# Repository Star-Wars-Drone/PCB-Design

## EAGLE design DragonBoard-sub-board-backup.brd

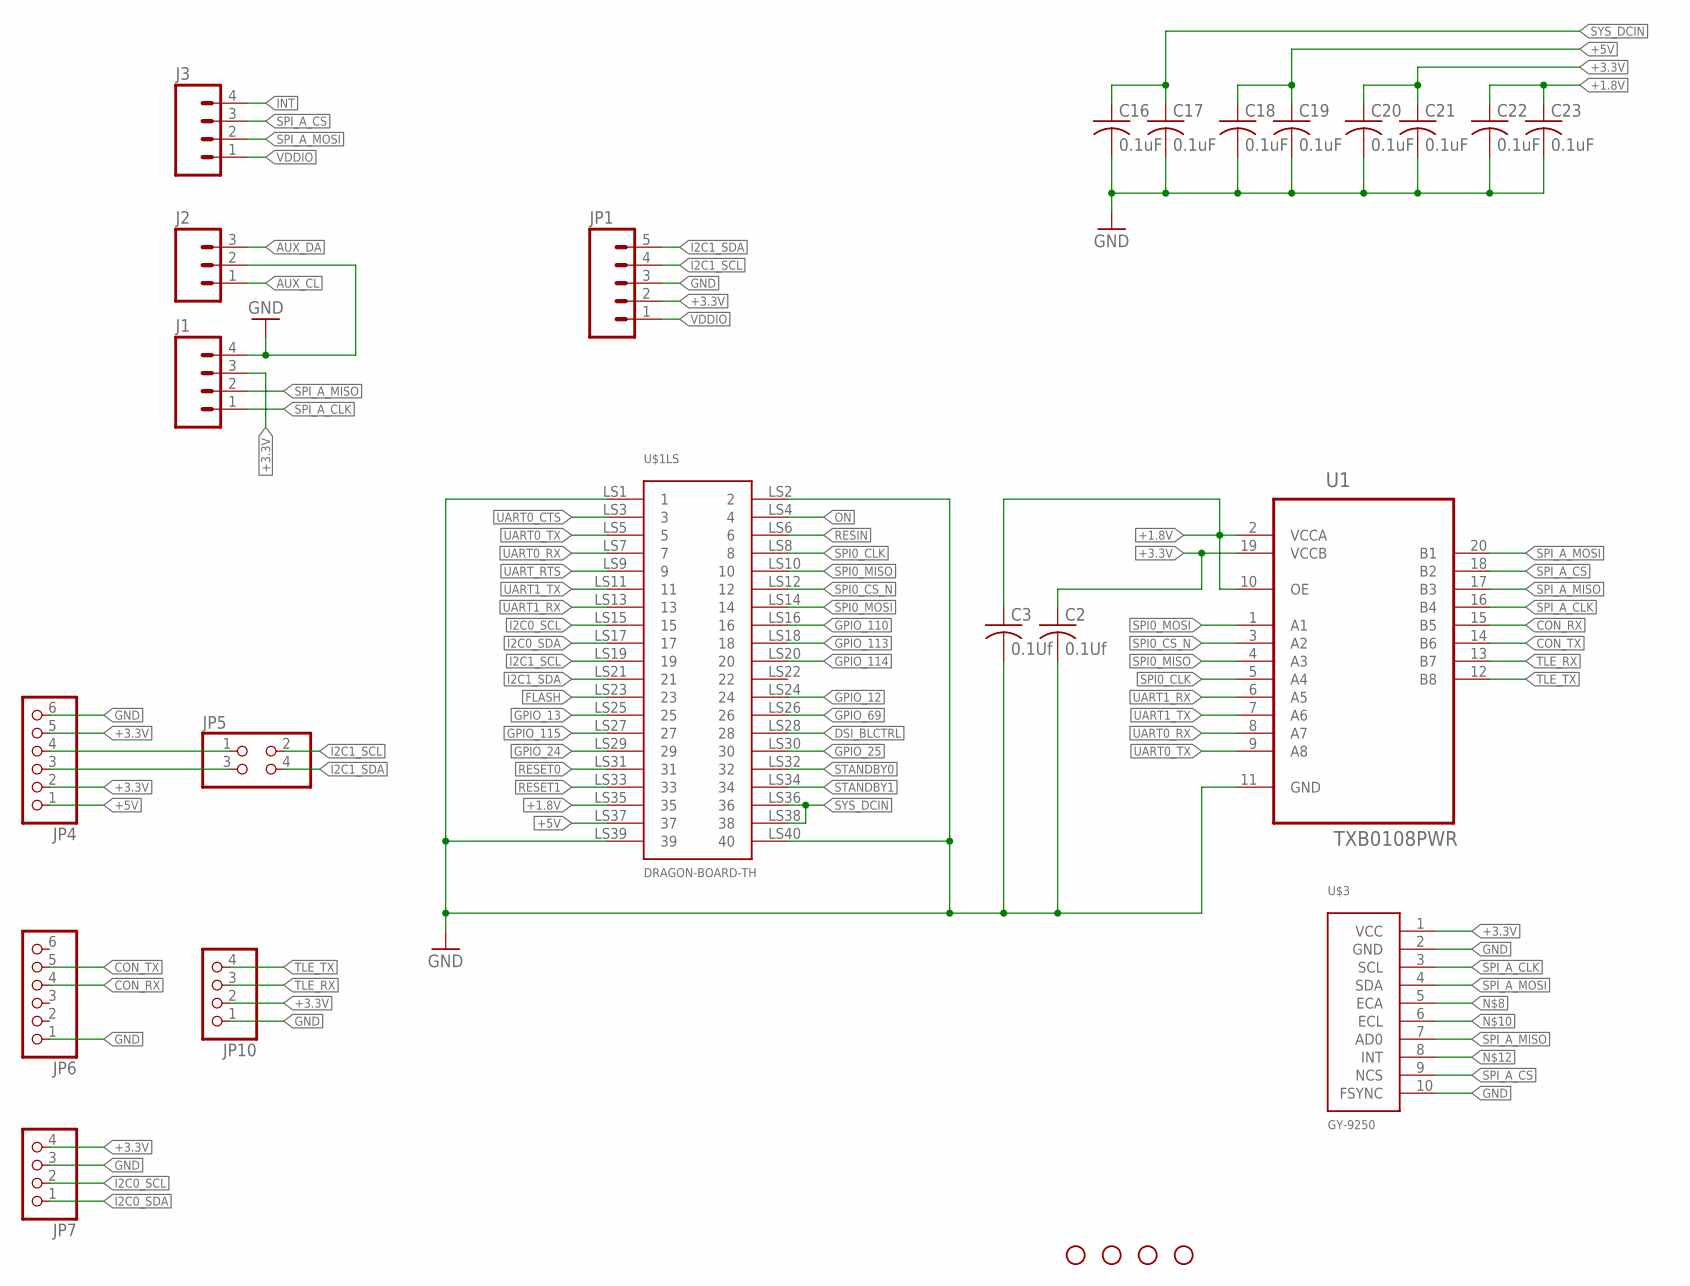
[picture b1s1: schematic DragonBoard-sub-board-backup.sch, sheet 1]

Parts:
C2, C3: 0.1Uf; C0402
C16, C17, C18, C19, C20, C21, C22, C23: 0.1uF; C0402
J1, J3: M04PTH; 1X04
J2: M03PTH; 1X03
JP1: M05_ROUNDONLY_NOSILK; 1X05_ROUNDONLY_NOSILK
JP4, JP6: PINHD-1X6; 1X06
JP5: PINHD-2X2; 2X02
JP7, JP10: PINHD-1X4; 1X04
STANDOFF1, STANDOFF2, STANDOFF3, STANDOFF4: STAND-OFF
U1: TXB0108PWR; SOP65P640X120-20N
U$1: DRAGON-BOARD-TH; DROGENBOARD-TH
U$3: GY-9250; IMU

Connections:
+1.8V: C3.1, C22.1, C23.1, U1.2 (VCCA), U1.10 (OE), U$1.LS35 (35); also elsewhere on the board
+3.3V: C2.1, C20.1, C21.1, J1.3, JP1.2, JP4.2, JP4.5, JP7.4, JP10.2, U1.19 (VCCB), U$3.1 (VCC); also elsewhere on the board
+5V: C18.1, C19.1, JP4.1, U$1.LS37 (37); also elsewhere on the board
AUX_CL: J2.1
AUX_DA: J2.3
CON_RX: JP6.4, U1.15 (B5)
CON_TX: JP6.5, U1.14 (B6)
DSI_BLCTRL: U$1.LS28 (28)
FLASH: U$1.LS23 (23); also elsewhere on the board
GND: C2.2, C3.2, C16.2, C17.2, C18.2, C19.2, C20.2, C21.2, C22.2, C23.2, J1.4, J2.2, JP1.3, JP4.6, JP6.1, JP7.3, JP10.1, U1.11 (GND), U$1.LS1 (1), U$1.LS2 (2), U$1.LS39 (39), U$1.LS40 (40), U$3.2 (GND), U$3.10 (FSYNC); also elsewhere on the board
GPIO_12: U$1.LS24 (24)
GPIO_13: U$1.LS25 (25)
GPIO_24: U$1.LS29 (29)
GPIO_25: U$1.LS30 (30)
GPIO_69: U$1.LS26 (26)
GPIO_110: U$1.LS16 (16)
GPIO_113: U$1.LS18 (18)
GPIO_114: U$1.LS20 (20)
GPIO_115: U$1.LS27 (27)
I2C0_SCL: JP7.2, U$1.LS15 (15)
I2C0_SDA: JP7.1, U$1.LS17 (17)
I2C1_SCL: JP1.4, JP5.2, U$1.LS19 (19); also elsewhere on the board
I2C1_SDA: JP1.5, JP5.4, U$1.LS21 (21); also elsewhere on the board
INT: J3.4
unnamed: JP4.4, JP5.1
unnamed: JP4.3, JP5.3
ON: U$1.LS4 (4)
RESET0: U$1.LS31 (31); also elsewhere on the board
RESET1: U$1.LS33 (33); also elsewhere on the board
RESIN: U$1.LS6 (6)
SPI0_CLK: U1.5 (A4), U$1.LS8 (8)
SPI0_CS_N: U1.3 (A2), U$1.LS12 (12)
SPI0_MISO: U1.4 (A3), U$1.LS10 (10)
SPI0_MOSI: U1.1 (A1), U$1.LS14 (14)
SPI_A_CLK: J1.1, U1.16 (B4), U$3.3 (SCL)
SPI_A_CS: J3.3, U1.18 (B2), U$3.9 (NCS)
SPI_A_MISO: J1.2, U1.17 (B3), U$3.7 (AD0)
SPI_A_MOSI: J3.2, U1.20 (B1), U$3.4 (SDA)
STANDBY0: U$1.LS32 (32); also elsewhere on the board
STANDBY1: U$1.LS34 (34); also elsewhere on the board
SYS_DCIN: C16.1, C17.1, U$1.LS36 (36), U$1.LS38 (38); also elsewhere on the board
TLE_RX: JP10.3, U1.13 (B7)
TLE_TX: JP10.4, U1.12 (B8)
UART0_CTS: U$1.LS3 (3)
UART0_RX: U1.8 (A7), U$1.LS7 (7)
UART0_TX: U1.9 (A8), U$1.LS5 (5)
UART1_RX: U1.6 (A5), U$1.LS13 (13)
UART1_TX: U1.7 (A6), U$1.LS11 (11)
UART_RTS: U$1.LS9 (9)
VDDIO: J3.1, JP1.1

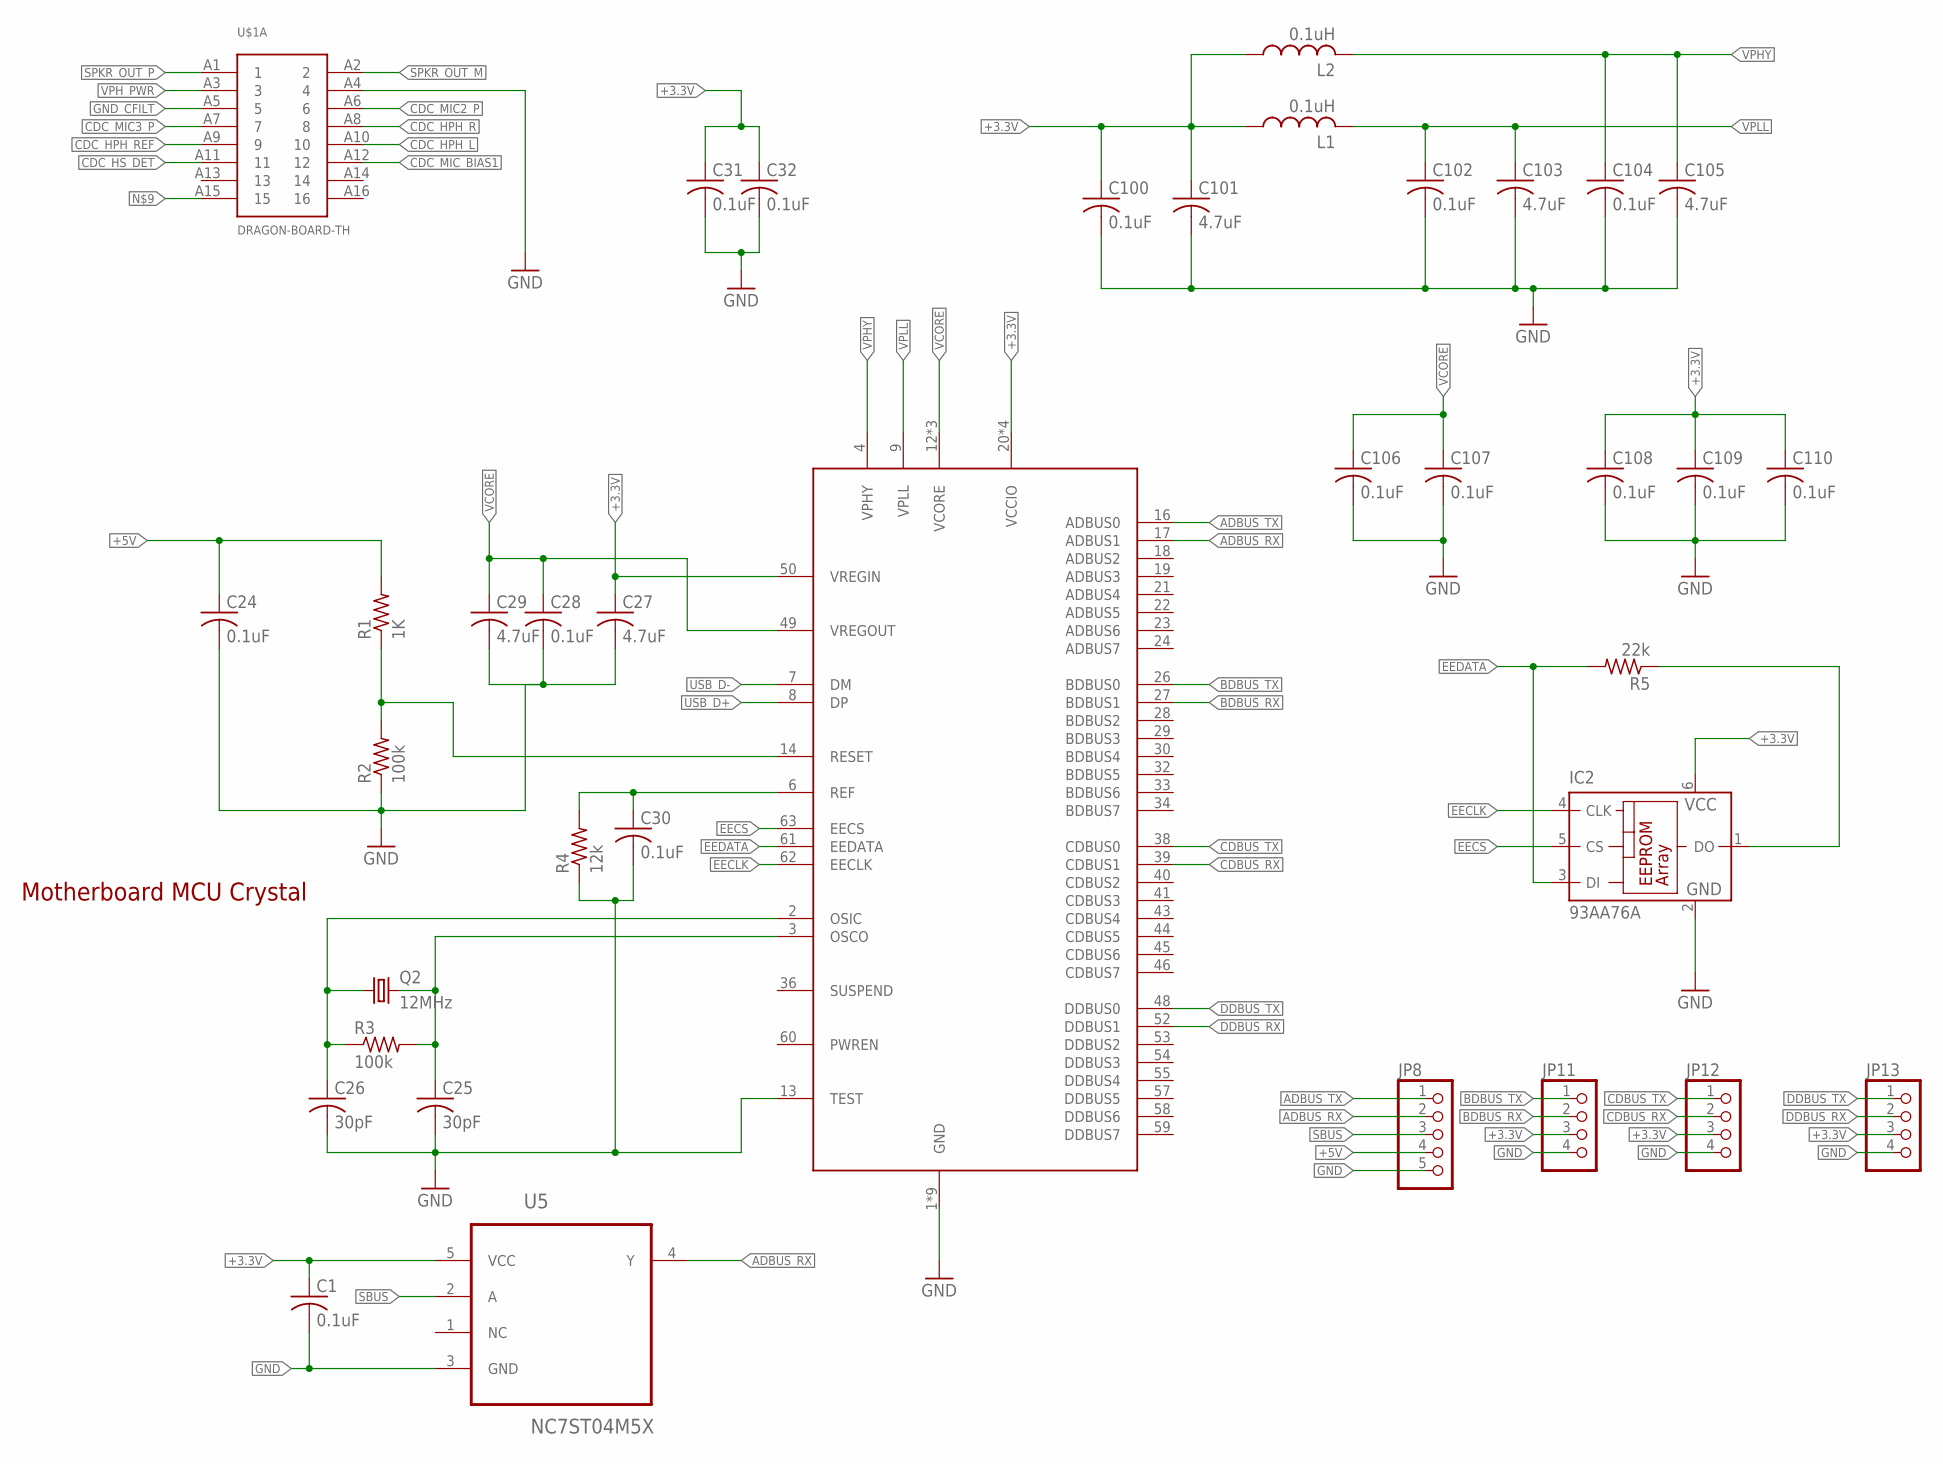
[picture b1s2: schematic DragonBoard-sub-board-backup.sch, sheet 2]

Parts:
C1, C24, C28, C30, C100, C102, C104, C106, C107, C108, C109, C110: 0.1uF; C0402
C25, C26: 30pF; C0402
C27, C29, C101, C103, C105: 4.7uF; C0402
C31, C32: 0.1uF; C0805
IC2: 93AA76A; SOT23-6
JP8: PINHD-1X5; 1X05
JP11, JP12, JP13: PINHD-1X4; 1X04
L1, L2: 0.1uH; L3216C
Q2: 12MHz; CTS406
R1: 1K; R0402
R2, R3: 100k; R0402
R4: 12k; R0402
R5: 22k; R0402
U5: NC7ST04M5X; SOT95P280X145-5N
U$1: DRAGON-BOARD-TH; DROGENBOARD-TH
U$4: FT423H; LQFP-64

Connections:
+3.3V: C1.1, C27.1, C31.1, C32.1, C100.1, C101.1, C108.1, C109.1, C110.1, IC2.6 (VCC), JP11.3, JP12.3, JP13.3, L1.1, L2.1, U5.5 (VCC), U$4.20 (VCCIO), U$4.31 (VCCIO), U$4.42 (VCCIO), U$4.50 (VREGIN), U$4.56 (VCCIO); also elsewhere on the board
+5V: C24.1, JP8.4, R1.2; also elsewhere on the board
ADBUS_RX: JP8.2, U5.4 (Y), U$4.17 (ADBUS1)
ADBUS_TX: JP8.1, U$4.16 (ADBUS0)
BDBUS_RX: JP11.2, U$4.27 (BDBUS1)
BDBUS_TX: JP11.1, U$4.26 (BDBUS0)
CDBUS_RX: JP12.2, U$4.39 (CDBUS1)
CDBUS_TX: JP12.1, U$4.38 (CDBUS0)
CDC_HPH_L: U$1.A10 (10)
CDC_HPH_R: U$1.A8 (8)
CDC_HPH_REF: U$1.A9 (9)
CDC_HS_DET: U$1.A11 (11)
CDC_MIC2_P: U$1.A6 (6)
CDC_MIC3_P: U$1.A7 (7)
CDC_MIC_BIAS1: U$1.A12 (12)
DDBUS_RX: JP13.2, U$4.52 (DDBUS1)
DDBUS_TX: JP13.1, U$4.48 (DDBUS0)
EECLK: IC2.4 (CLK), U$4.62 (EECLK)
EECS: IC2.5 (CS), U$4.63 (EECS)
EEDATA: IC2.3 (DI), R5.2, U$4.61 (EEDATA)
GND: C1.2, C24.2, C25.2, C26.2, C27.2, C28.2, C29.2, C30.2, C31.2, C32.2, C100.2, C101.2, C102.2, C103.2, C104.2, C105.2, C106.2, C107.2, C108.2, C109.2, C110.2, IC2.2 (GND), JP8.5, JP11.4, JP12.4, JP13.4, R2.1, R4.1, U5.3 (GND), U$1.A4 (4), U$4.1 (GND), U$4.5 (GND), U$4.10 (GND), U$4.11 (GND), U$4.13 (TEST), U$4.15 (GND), U$4.25 (GND), U$4.35 (GND), U$4.47 (GND), U$4.51 (GND); also elsewhere on the board
GND_CFILT: U$1.A5 (5)
unnamed: C30.1, R4.2, U$4.6 (REF)
unnamed: C26.1, Q2.1, R3.1, U$4.2 (OSIC)
unnamed: C25.1, Q2.3 (2), R3.2, U$4.3 (OSCO)
unnamed: IC2.1 (DO), R5.1
unnamed: R1.1, R2.2, U$4.14 (RESET)
SBUS: JP8.3, U5.2 (A)
SPKR_OUT_M: U$1.A2 (2)
SPKR_OUT_P: U$1.A1 (1)
USB_D+: U$4.8 (DP); also elsewhere on the board
USB_D-: U$4.7 (DM); also elsewhere on the board
VCORE: C28.1, C29.1, C106.1, C107.1, U$4.12 (VCORE), U$4.37 (VCORE), U$4.49 (VREGOUT), U$4.64 (VCORE)
VPHY: C104.1, C105.1, L2.2, U$4.4 (VPHY)
VPH_PWR: U$1.A3 (3)
VPLL: C102.1, C103.1, L1.2, U$4.9 (VPLL)

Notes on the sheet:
Motherboard MCU Crystal

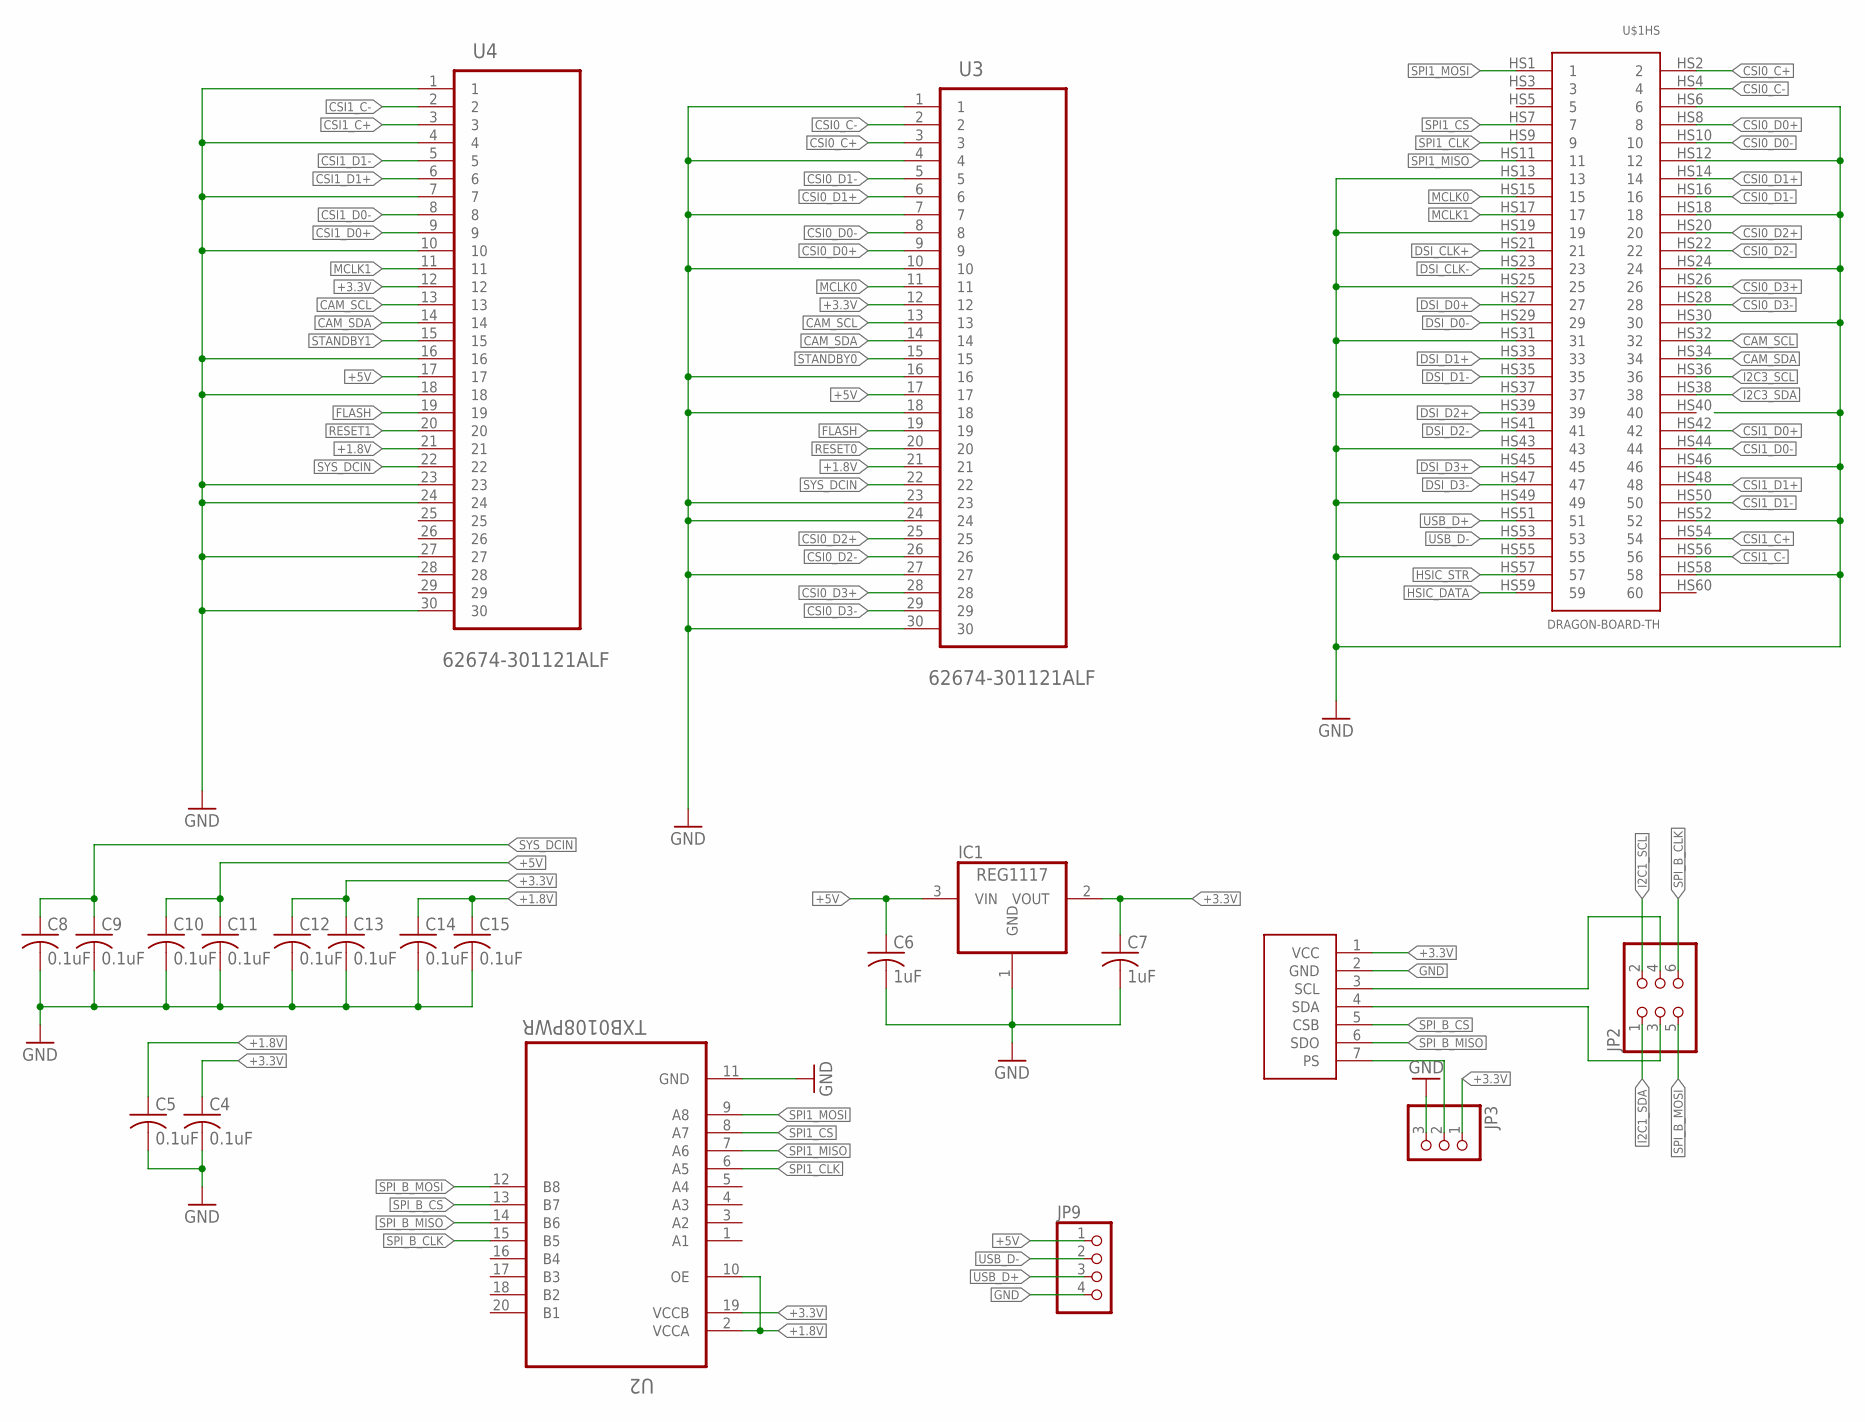
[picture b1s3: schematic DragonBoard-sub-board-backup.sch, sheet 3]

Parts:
C4, C5, C8, C9, C10, C11, C12, C13, C14, C15: 0.1uF; C0402
C6, C7: 1uF; C0402
IC1: REG1117; SOT223
JP2: PINHD-2X3; 2X03
JP3: PINHD-1X3; 1X03
JP9: PINHD-1X4; 1X04
U2: TXB0108PWR; SOP65P640X120-20N
U3, U4: 62674-301121ALF; FCI_62674-301121ALF
U$1: DRAGON-BOARD-TH; DROGENBOARD-TH
U$2: GY-63; BURO

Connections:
+1.8V: C5.1, C14.1, C15.1, U2.2 (VCCA), U2.10 (OE), U3.21, U4.21; also elsewhere on the board
+3.3V: C4.1, C7.1, C12.1, C13.1, IC1.2 (VOUT), JP3.1, U2.19 (VCCB), U3.12, U4.12, U$2.1 (VCC); also elsewhere on the board
+5V: C6.1, C10.1, C11.1, IC1.3 (VIN), JP9.1, U3.17, U4.17; also elsewhere on the board
CAM_SCL: U3.13, U4.13, U$1.HS32 (32)
CAM_SDA: U3.14, U4.14, U$1.HS34 (34)
CSI0_C+: U3.3, U$1.HS2 (2)
CSI0_C-: U3.2, U$1.HS4 (4)
CSI0_D0+: U3.9, U$1.HS8 (8)
CSI0_D0-: U3.8, U$1.HS10 (10)
CSI0_D1+: U3.6, U$1.HS14 (14)
CSI0_D1-: U3.5, U$1.HS16 (16)
CSI0_D2+: U3.25, U$1.HS20 (20)
CSI0_D2-: U3.26, U$1.HS22 (22)
CSI0_D3+: U3.28, U$1.HS26 (26)
CSI0_D3-: U3.29, U$1.HS28 (28)
CSI1_C+: U4.3, U$1.HS54 (54)
CSI1_C-: U4.2, U$1.HS56 (56)
CSI1_D0+: U4.9, U$1.HS42 (42)
CSI1_D0-: U4.8, U$1.HS44 (44)
CSI1_D1+: U4.6, U$1.HS48 (48)
CSI1_D1-: U4.5, U$1.HS50 (50)
DSI_CLK+: U$1.HS21 (21)
DSI_CLK-: U$1.HS23 (23)
DSI_D0+: U$1.HS27 (27)
DSI_D0-: U$1.HS29 (29)
DSI_D1+: U$1.HS33 (33)
DSI_D1-: U$1.HS35 (35)
DSI_D2+: U$1.HS39 (39)
DSI_D2-: U$1.HS41 (41)
DSI_D3+: U$1.HS45 (45)
DSI_D3-: U$1.HS47 (47)
FLASH: U3.19, U4.19; also elsewhere on the board
GND: C4.2, C5.2, C6.2, C7.2, C8.2, C9.2, C10.2, C11.2, C12.2, C13.2, C14.2, C15.2, IC1.1 (GND), JP3.3, JP9.4, U2.11 (GND), U3.1, U3.4, U3.7, U3.10, U3.16, U3.18, U3.23, U3.24, U3.27, U3.30, U4.1, U4.4, U4.7, U4.10, U4.16, U4.18, U4.23, U4.24, U4.27, U4.30, U$1.HS6 (6), U$1.HS12 (12), U$1.HS13 (13), U$1.HS18 (18), U$1.HS19 (19), U$1.HS24 (24), U$1.HS25 (25), U$1.HS30 (30), U$1.HS31 (31), U$1.HS37 (37), U$1.HS43 (43), U$1.HS46 (46), U$1.HS49 (49), U$1.HS52 (52), U$1.HS55 (55), U$1.HS58 (58), U$2.2 (GND); also elsewhere on the board
HSIC_DATA: U$1.HS59 (59)
HSIC_STR: U$1.HS57 (57)
I2C1_SCL: JP2.2; also elsewhere on the board
I2C1_SDA: JP2.1; also elsewhere on the board
I2C3_SCL: U$1.HS36 (36)
I2C3_SDA: U$1.HS38 (38)
MCLK0: U3.11, U$1.HS15 (15)
MCLK1: U4.11, U$1.HS17 (17)
unnamed: JP3.2, U$2.7 (PS)
unnamed: JP2.3, U$2.4 (SDA)
unnamed: JP2.4, U$2.3 (SCL)
RESET0: U3.20; also elsewhere on the board
RESET1: U4.20; also elsewhere on the board
SPI1_CLK: U2.6 (A5), U$1.HS9 (9)
SPI1_CS: U2.8 (A7), U$1.HS7 (7)
SPI1_MISO: U2.7 (A6), U$1.HS11 (11)
SPI1_MOSI: U2.9 (A8), U$1.HS1 (1)
SPI_B_CLK: JP2.6, U2.15 (B5)
SPI_B_CS: U2.13 (B7), U$2.5 (CSB)
SPI_B_MISO: U2.14 (B6), U$2.6 (SDO)
SPI_B_MOSI: JP2.5, U2.12 (B8)
STANDBY0: U3.15; also elsewhere on the board
STANDBY1: U4.15; also elsewhere on the board
SYS_DCIN: C8.1, C9.1, U3.22, U4.22; also elsewhere on the board
USB_D+: JP9.3, U$1.HS51 (51); also elsewhere on the board
USB_D-: JP9.2, U$1.HS53 (53); also elsewhere on the board

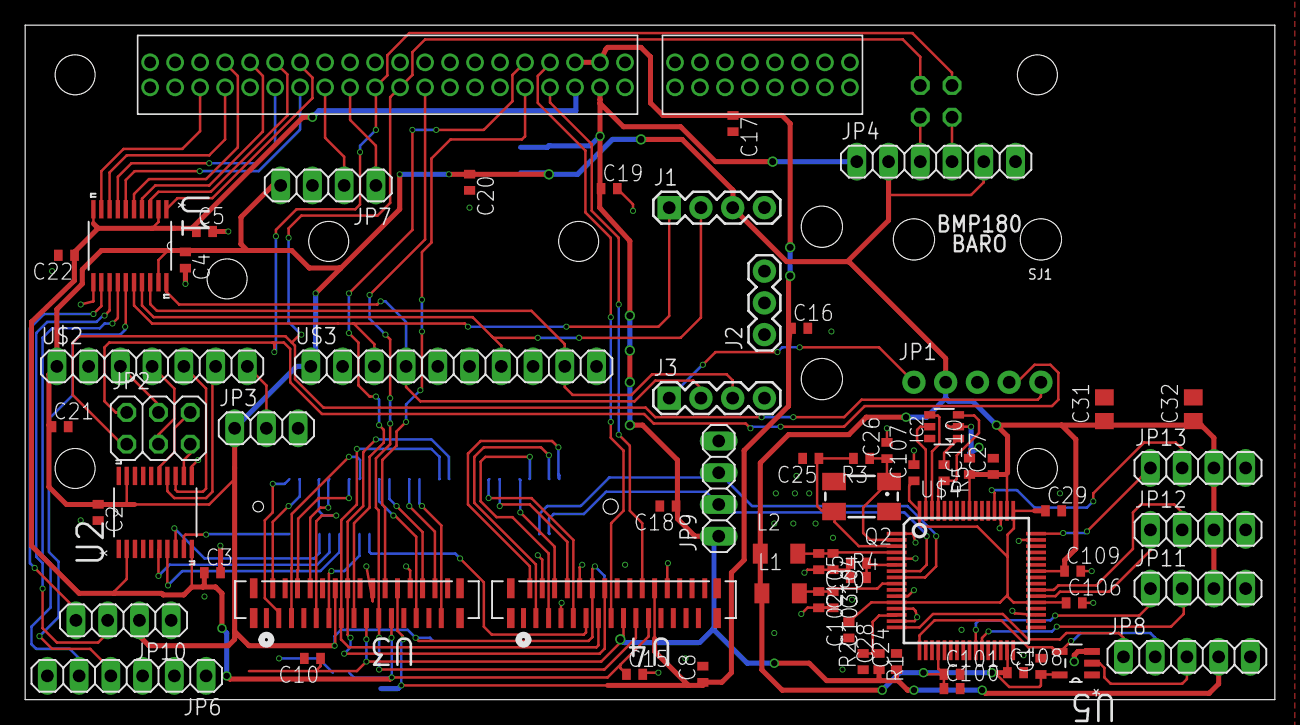
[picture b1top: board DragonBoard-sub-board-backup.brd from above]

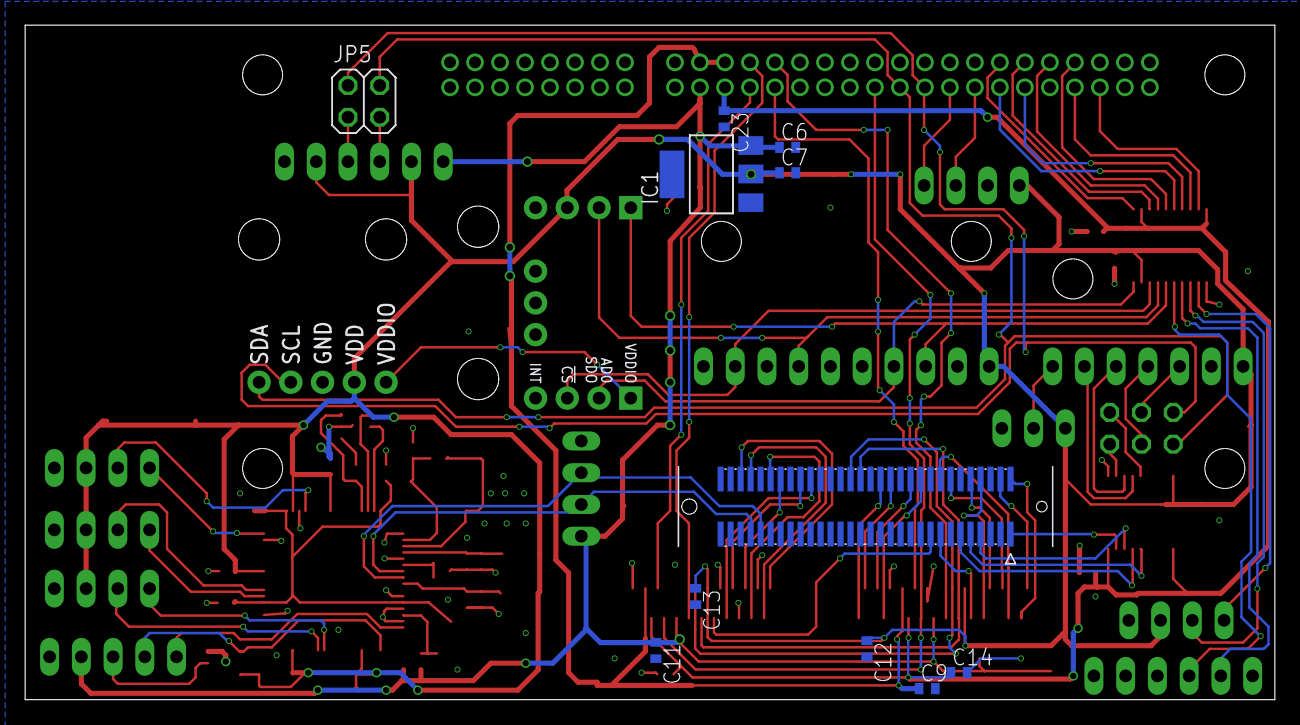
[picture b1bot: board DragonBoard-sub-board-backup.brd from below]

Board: 2 copper layers, 100.0 x 54.0 mm, 82 parts (10 on the bottom side), 86 nets.

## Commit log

2017-02-08 added ftdi chip
2017-02-08 FIXED pin outs for ftdi chip
2017-02-09 Fixed missing traces and some values. Also added bmp logos.
2017-02-09 Fixed more of Josh's fuck ups.
2017-02-09 Done with baord

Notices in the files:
parts and their libraries:
SparkFun-Electromechanical: Licensing: CC v3.0 Share-Alike You are welcome to use this library for commercial purposes.
SparkFun-Connectors: Licensing: Creative Commons ShareAlike 4.0 International - https://creativecommons.org/licenses/by-sa/4.0
